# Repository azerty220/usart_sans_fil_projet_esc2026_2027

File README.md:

# Projet de Transmission UART Sans Fil

Projet Système réalisé en troisième année spécialité Electronique et Systèmes de Communication à l'ENSEA : 

> Mise en place d'une communication sans fil USART avec un drône

## Cahier des charges

L'objectif de ce projet est de concevoir une chaîne de transmission/réception RF à partir de composants existants. Cet émetteur-récepteur est destiné à la communication avec un drone. Il y a donc une contrainte de place sur au moins une des versions du système.

Contraintes générales :

    Portée du système : 10m
    Durée du projet : 40h
    Budget : 250€

Paramètres de l'USART fourni : 

    Débit : 115 200 baud
    8 bits de données
    1 bit de parité (pair)
    1 bit de stop

## Choix de la fréquence porteuse et de la modulation

Nous avons choisi une porteuse à **868MHz**, ainsi que la modulation **ASK**,    

- Notre choix s'est porté sur la modulation ASK afin d'obtenir une portée nettement supérieure. De plus, nous avons pris en compte l'expérience d'un groupe ayant réalisé ce même projet en 2025 avec la modulation BPSK : leur choix avait entraîné de lourdes difficultés, notamment au niveau de la démodulation et de la récupération de la porteuse en phase. Cette dernière nécessitait en effet une PLL sans erreur de phase, alors qu'une PLL est initialement conçue pour minimiser les erreurs de fréquence.    
- En ce qui concerne la fréquence, nous avons choisi de réutiliser les composants des années précédentes afin de réduire les coûts. De plus, opter pour la bande des 2,4 GHz très proche de la bande Wi-Fi nous aurait exposé à de nombreux signaux parasites, qui auraient été difficiles à filtrer.

# Vue d'ensemble du système émission/réception

Voici une description de notre système. Celui-ci s'organise autour d'une chaîne d'émission (composée du modulateur ASK, du PA et du filtrage) et d'une chaîne de réception (composée du filtrage, du LNA et du démodulateur ASK). Pour permettre l'utilisation d'une seule antenne dans les deux modes, les deux chaînes sont reliées par un Switch RF qui permet de passer d'un mode à l'autre. L'ensemble est piloté par un microcontrôleur µC et la porteuse elle est générée par l'oscillateur local :    

Dans un premier temps, nous avons découpé le système par fonctions : chaque binôme s'est vu assigner une tâche spécifique et devait réaliser un premier PCB (2 couches) dédié. Dans un second temps, une fois les tests validés, un PCB unique à 4 couches a été conçu pour regrouper l'ensemble du système.

# Description de la chaîne d'émission

Le rôle principal de la chaîne d'émission, consiste à traiter les données numériques reçues par liaison UART, à générer une porteuse radiofréquence à 868 MHz (stabilisée par un oscillateur local à boucle à verrouillage de phase (PLL)), puis à appliquer une modulation d'amplitude de type ASK (Amplitude Shift Keying). Le signal ainsi modulé traverse ensuite un étage de filtrage avant d'être acheminé vers l'antenne.
    <br>Le développement de cette chaîne d'émission a été structuré autour de plusieurs objectifs clés :
        <br> 1- Garantir l'intégrité et la fiabilité de la transmission des données numériques via l'interface UART.
        <br> 2- Produire un signal porteur RF stable, propre et paramétrable.
        <br> 3- Exécuter une modulation ASK fidèle aux trames de données à transmettre.
        <br> 4- Filtrer efficacement le signal radiofréquence pour respecter les normes en vigueur avant son émission par l'antenne.

## Bloc génération de la porteuse et modulation ASK

Cette partie décrit le fonctionnement des premiers bloc (Modulateur ASK et Oscillateur Local) de la chaîne détaillée précédemment, la génération de la porteuse sera réalisée par le synthétiseur de fréquence à boucle à verrouillage de phase (PLL) l’ADF4350, afin d’avoir une référence de fréquence, ce dernier sera relié à l’oscillateur ECS-TXD-20CSMV-AC-260-AY-TR et enfin pour réaliser la modulation ASK, nous utiliserons un switch RF, l’ADG918BCPZ.

### 1- interface Nucléo/PCB RF

La communication entre la carte microcontrôleur (Nucleo STM32) et le PCB RF est assurée par plusieurs connecteurs dédiés :

    <br>• Connecteur d'interface SPI (J2) : regroupant les signaux de configuration SCK (horloge de communication), DATA (données de configuration), LE (validation du registre sélectionné) et CE (activation du composant), ainsi que la masse GND, permettant le paramétrage du synthétiseur de fréquence.
    <br>• Connecteur de commande (J3) : acheminant le signal de commande UART_RX issu du microcontrôleur vers le modulateur ASK.
   <br> • Connecteur d'alimentation (J6) : fournissant les tensions +3.3V, +2V5 (utiles pour alimenter l’ADF4350, ADG918 et l’oscillateur) et la référence de masse GND à la carte.

<br>La configuration du synthétiseur de fréquence ADF4350 (U1) est réalisée via une interface série synchrone de type SPI. Cette interface permet notamment :
   <br> • l’écriture des registres de configuration de la PLL
   <br> • l’initialisation et la réinitialisation du composant
   <br> • la reprogrammation dynamique de la fréquence de sortie.

### 2- Génération de la porteuse

La génération de la porteuse radiofréquence est assurée par le composant ADF4350 (U1) d’Analog Devices. Ce circuit intègre un oscillateur commandé en tension (VCO) interne couvrant une large plage de fréquences, ainsi que l’ensemble des blocs nécessaires à la réalisation d’une PLL fractionnaire ou entière. 
<br>La référence de fréquence (26MHz) est fournie par l’oscillateur à quartz Y1 (ECS-TXD-20CSMV-AC-260-AY-TR) connecté à l’entrée REFIN via le condensateur C24 (capacité bouchon de 1 nF). Dans cette application, l’ADF4350 est configuré pour fournir une porteuse à 868 MHz.

### 3- Modulation ASK
<br>-> SMA vers le PCB amplificateur de puissance et filtrage
<br> Vue d'ensemble du PCB

## Bloc amplificateur de puissance et filtrage

La sortie du modulateur est réglable en puissance entre -4dBm et 5dBm, ce qui n'est pas suffisant pour atteindre la portée voulue. 

Nous avions en stock des amplificateurs SKY66185-11, utilisés pour un projet semblable l'année précédente. Ces amplificateurs Skyworks à forte linéarité fournissent un gain supplémentaire de $36.5$ dB, sur une bande de  $851$ à $894$ MHz.

> Bilan de puissance à faire

Ce signal amplifié passe ensuite dans un filtre de mise en forme, le SF2425E.

Premier PCB de test :

# Switch RF et antenne

Commutation entre les 2 modes -> Johan

# Description de la chaîne de réception

choix des composants modules par module

## Bloc filtrage et LNA

Le signal capté par l'antenne est amplifié par le LNA **GRF2070**, puis filtré par le filtre SAW **SF2425E** centré sur 868,6 MHz.

```mermaid
flowchart LR
    A((Antenne)) --> LNA[["LNA GRF2070<br/>G = 21 dB · NF = 0,4 dB"]]
    LNA --> SAW[["Filtre SAW SF2425E<br/>BP ≈ 1,5 MHz · IL ≈ 2,65 dB"]]
    SAW --> D[Démodulateur ASK]
    style LNA fill:#dbeafe,stroke:#2563eb
    style SAW fill:#dcfce7,stroke:#16a34a
```

<p align="center">

| Réf.            | Valeur                        | Rôle                                                |
|:---------------:|:-----------------------------:|:--------------------------------------------------- |
| C1 / C2         | 47 pF / 4,7 pF                | Liaison entrée / sortie du LNA (blocage du continu) |
| R2              | 910 Ω                         | Polarisation : fixe I<sub>DD</sub> ≈ 70 mA sous 5 V |
| L1              | 22 nH                         | Self de choc : amène le 5 V sur `RF_OUT/VDD`        |
| C3 / C4         | 100 nF / 100 pF               | Découplage BF / HF                                  |
| L2, C6 / L3, C7 | 22 nH, 2,7 pF / 33 nH, 3,9 pF | Adaptation 50 Ω ↔ filtre SAW (≈ 386 Ω ∥ 1,6 pF)     |

**Pourquoi LNA → filtre ?** D'après la formule de Friis, $F = F_1 + (F_2-1)/G_1$. Placé derrière 21 dB de gain, le filtre ne dégrade presque pas le bruit : **NF ≈ 0,43 dB**, contre ≈ 3 dB si le filtre était placé avant le LNA. Le signal ASK à 115,2 kbaud occupe environ 230 kHz et passe sans déformation dans la bande de 1,5 MHz du filtre.

| Chaîne complète | Gain ≈ **18,4 dB** | NF ≈ **0,43 dB** | Alim. **5 V / 70 mA** |
|:--------------- |:------------------:|:----------------:|:---------------------:|

## Bloc Démodulateur

### 1. Présentation et choix du composant

Ce PCB a été conçu sous **KiCad 9.0** pour réaliser la démodulation d'un signal radiofréquence modulé en amplitude (**ASK**), dans le cadre du projet de transmission USART sans fil entre une station au sol et un drone.

Le circuit repose sur l'**AD8313 d'Analog Devices**, un détecteur logarithmique RF fonctionnant sur une plage de fréquences de **100 MHz à 2,5 GHz**.

Ce composant a été choisi pour :

- Sa compatibilité avec les fréquences envisagées de **868 MHz et 918 MHz**.
- Sa capacité à détecter des signaux RF de faible puissance.
- Sa sortie analogique permettant de récupérer l'enveloppe du signal ASK.
- Son faible encombrement, adapté à la conception d'un PCB compact.

Le PCB intègre également un réseau d'adaptation RF, des condensateurs de découplage et un plan de masse sur la couche **B.Cu**.

### 2. Connecteur SMA – Entrée RF (J2)

Le connecteur **SMA J2** constitue l'entrée radiofréquence du PCB.

Il permet de raccorder une antenne ou un générateur RF à l'aide d'un câble coaxial de **50 Ω**.

Le signal reçu traverse le condensateur de liaison **C2 (680 pF)**, qui bloque la composante continue, avant d'atteindre l'entrée **INHI** de l'AD8313.

La résistance **R2 (53,6 Ω)** participe à l'adaptation de l'entrée RF à une impédance proche de 50 Ω afin de limiter les réflexions.

Le connecteur SMA a été choisi pour faciliter les tests avec les équipements RF disponibles au laboratoire.

### 3. Connecteur J3 – Alimentation et sortie démodulée

Le connecteur **J3 à trois broches** regroupe l'alimentation, la masse et la sortie du démodulateur.

| Broche | Signal    | Fonction                    |
| ------ | --------- | --------------------------- |
| 1      | VCC_demod | Alimentation du circuit     |
| 2      | GND       | Masse commune               |
| 3      | demodOUT  | Sortie analogique démodulée |

L'alimentation des deux broches **VPOS** de l'AD8313 passe par les résistances **R1 et R3 (10 Ω)**, associées aux condensateurs de découplage **C1 et C4 (100 nF)** pour réduire les perturbations sur l'alimentation.

La sortie **VOUT** est reliée à **VSET** par une résistance de **0 Ω (R4)** et traverse une résistance de protection **Rprot1 (500 Ω)** avant d'atteindre le connecteur J3.

Une résistance **RL1 (1 MΩ)** est également connectée entre la sortie et la masse.

Ce connecteur facilite l'intégration du démodulateur avec les autres blocs du système de communication.
Voici sa visualisation en 3D

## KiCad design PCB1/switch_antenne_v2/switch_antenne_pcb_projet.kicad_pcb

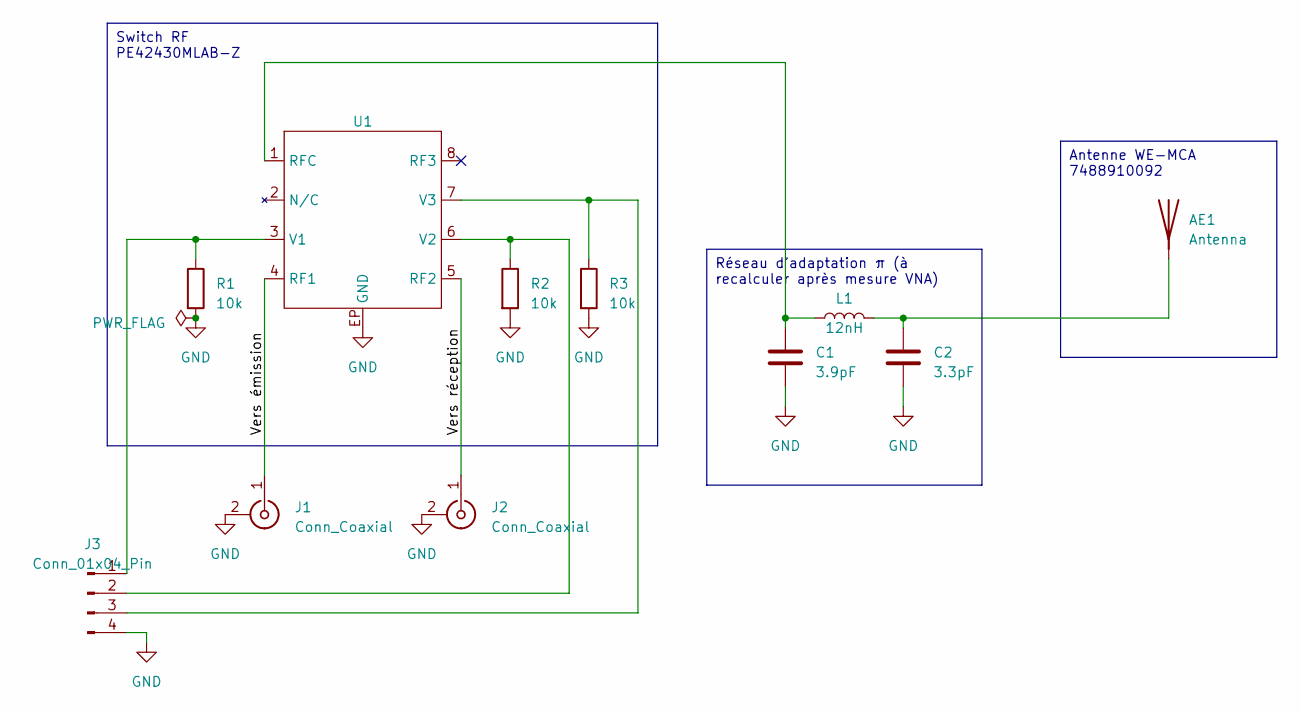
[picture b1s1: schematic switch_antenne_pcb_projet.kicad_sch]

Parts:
AE1: Antenna; AE_Wurth_WE-MCA_7488910092
C1: 3.9pF; C_0402_1005Metric_Pad0.74x0.62mm_HandSolder
C2: 3.3pF; C_0402_1005Metric_Pad0.74x0.62mm_HandSolder
J1, J2: Conn_Coaxial; SMA_Samtec_SMA-J-P-X-ST-EM1_EdgeMount
J3: Conn_01x04_Pin; PinHeader_1x04_P2.54mm_Vertical
L1: 12nH; L_0402_1005Metric_Pad0.77x0.64mm_HandSolder
R1, R2, R3: 10k; R_0603_1608Metric_Pad0.98x0.95mm_HandSolder
U1: SON50P200X200X60-9N160X90

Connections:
/Vers réception: J2.1 (In), U1.5 (RF2)
/Vers émission: J1.1 (In), U1.4 (RF1)
GND: C1.2, C2.2, J1.2 (Ext), J2.2 (Ext), J3.4, R1.2, R2.2, R3.2, U1.EP (GND)
unnamed: AE1.2 (A), C2.1, L1.2
unnamed: J3.1, R1.1, U1.3 (V1)
unnamed: J3.2, R2.1, U1.6 (V2)
unnamed: J3.3, R3.1, U1.7 (V3)
unnamed: C1.1, L1.1, U1.1 (RFC)

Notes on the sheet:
Switch RF PE42430MLAB-Z
Réseau d’adaptation π (à recalculer après mesure VNA)
Antenne WE-MCA 7488910092

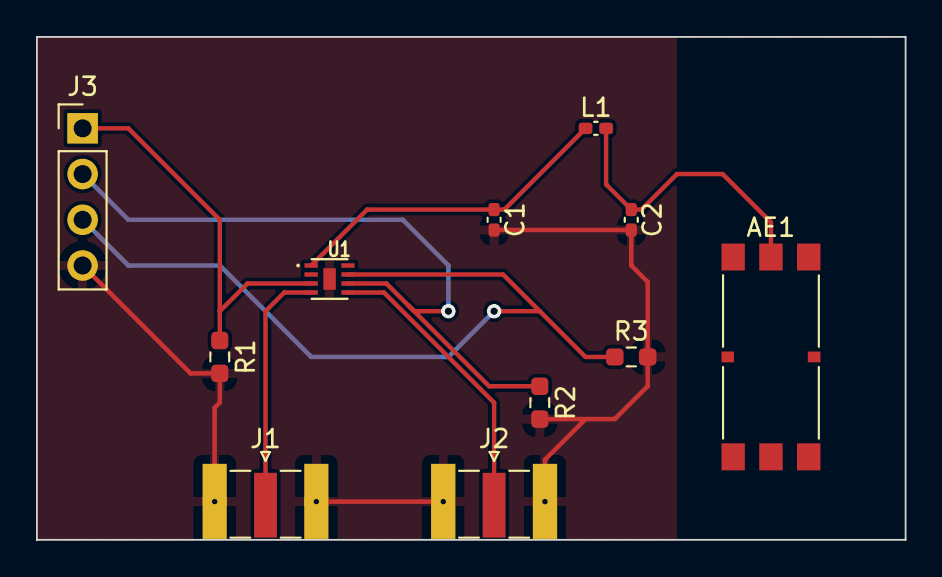
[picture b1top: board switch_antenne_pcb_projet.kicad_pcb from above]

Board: 2 copper layers, 48.3 x 27.9 mm, 11 parts (0 on the bottom side), 8 nets.

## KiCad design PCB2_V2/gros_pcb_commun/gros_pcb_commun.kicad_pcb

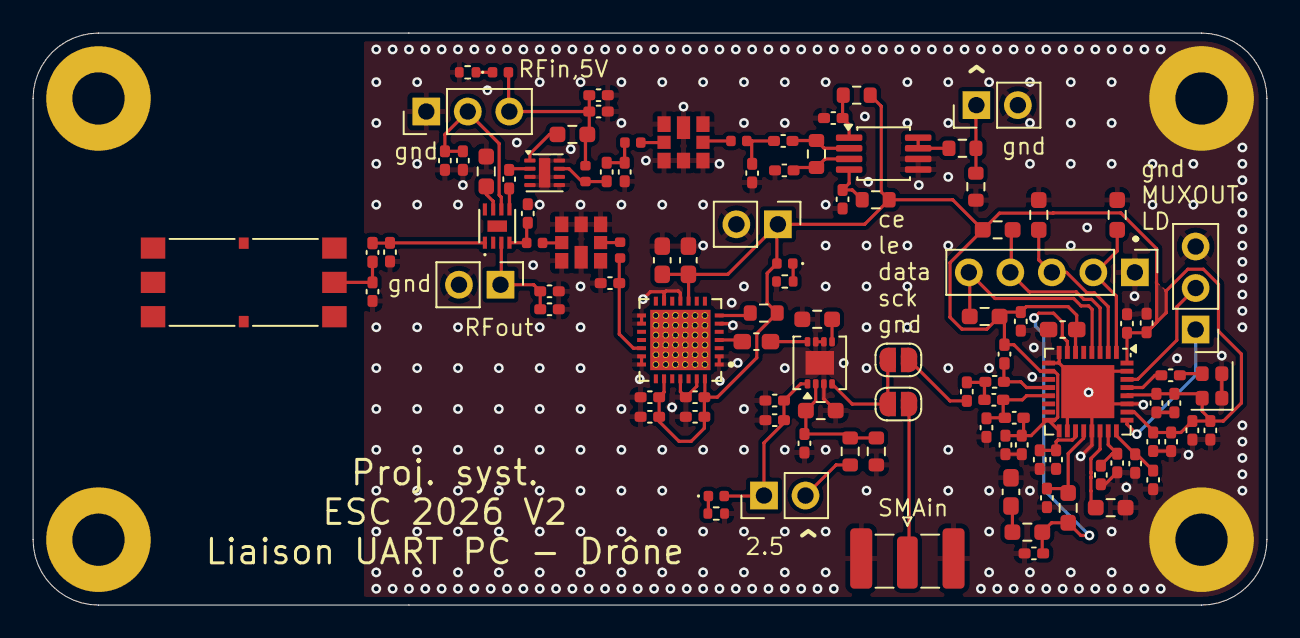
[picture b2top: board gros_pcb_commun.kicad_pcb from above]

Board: 2 copper layers, 75.5 x 35.0 mm, 111 parts (0 on the bottom side), 57 nets.

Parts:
AE1: Antenna; AE_Wurth_WE-MCA_7488910092
C1, C3, C5, C7, C9: 100 nF; C_0402_1005Metric_Pad0.74x0.62mm_HandSolder
C2, C4, C6, C10, C13, C15, C17, C27: 10 pF; C_0402_1005Metric_Pad0.74x0.62mm_HandSolder
C8: 10 pF; C_0603_1608Metric_Pad1.08x0.95mm_HandSolder
C11: 1 uF; C_0402_1005Metric_Pad0.74x0.62mm_HandSolder
C12, C14, C16, C18, C28, C42, C43: 0.1 uF; C_0402_1005Metric_Pad0.74x0.62mm_HandSolder
C19: 1 nF; C_0402_1005Metric_Pad0.74x0.62mm_HandSolder
C20, C21: 4 pF; C_0402_1005Metric_Pad0.74x0.62mm_HandSolder
C22: 120 pF; C_0402_1005Metric_Pad0.74x0.62mm_HandSolder
C23: 42.3 nF; C_0402_1005Metric_Pad0.74x0.62mm_HandSolder
C24: 575 nF; C_0603_1608Metric_Pad1.08x0.95mm_HandSolder
C25: 19.3 nF; C_0402_1005Metric_Pad0.74x0.62mm_HandSolder
C26: 100 pF; C_0402_1005Metric_Pad0.74x0.62mm_HandSolder
C29, C32, C35, C36, C50, C53: 0.1u; C_0402_1005Metric_Pad0.74x0.62mm_HandSolder
C30: 2.7p; C_0402_1005Metric_Pad0.74x0.62mm_HandSolder
C31: 33p; C_0603_1608Metric_Pad1.08x0.95mm_HandSolder
C33, C37: 10u; C_0603_1608Metric_Pad1.08x0.95mm_HandSolder
C34: 3.5p; C_0402_1005Metric_Pad0.74x0.62mm_HandSolder
C38: 3.9pF; C_0402_1005Metric_Pad0.74x0.62mm_HandSolder
C39: 3.3pF; C_0402_1005Metric_Pad0.74x0.62mm_HandSolder
C40, C41: 680 pF; C_0402_1005Metric_Pad0.74x0.62mm_HandSolder
C44: 47pF; C_0402_1005Metric_Pad0.74x0.62mm_HandSolder
C45: 4.7pF; C_0402_1005Metric_Pad0.74x0.62mm_HandSolder
C46: 100nF; C_0402_1005Metric_Pad0.74x0.62mm_HandSolder
C47: 100pF; C_0402_1005Metric_Pad0.74x0.62mm_HandSolder
C48: 2,7pF; C_0402_1005Metric_Pad0.74x0.62mm_HandSolder
C49: 3,5pF; C_0402_1005Metric_Pad0.74x0.62mm_HandSolder
C51, C52: 10u; C_0402_1005Metric_Pad0.74x0.62mm_HandSolder
D1, D2, D3: LED_Small; LED_0402_1005Metric
FL1: SF2425E
H1, H2, H3, H4: MountingHole_Pad; MountingHole_3.2mm_M3_Pad
J1, J2, J6, J7: Conn_01x02_Pin; PinHeader_1x02_P2.54mm_Vertical
J3: Conn_01x05; PinHeader_1x05_P2.54mm_Vertical
J4: Conn_01x03; PinHeader_1x03_P2.54mm_Vertical
J5: Conn_Coaxial; SMA_Samtec_SMA-J-P-H-ST-EM1_EdgeMount
J9: Conn_01x03_Pin; PinHeader_1x03_P2.54mm_Vertical
JP1, JP2: SolderJumper_2_Open; SolderJumper-2_P1.3mm_Open_RoundedPad1.0x1.5mm
L1: 68 nH; L_0402_1005Metric_Pad0.77x0.64mm_HandSolder
L2, L3: 18 nH; L_0402_1005Metric_Pad0.77x0.64mm_HandSolder
L4, L5: 24n; L_0402_1005Metric
L6: 12nH; L_0402_1005Metric_Pad0.77x0.64mm_HandSolder
L7, L8, L9: 22nH; L_0402_1005Metric
R1, R2, R3, R5, R8, R13: 10k; R_0603_1608Metric_Pad0.98x0.95mm_HandSolder
R4: 5.1 k; R_0603_1608Metric_Pad0.98x0.95mm_HandSolder
R6: 59.7; R_0603_1608Metric_Pad0.98x0.95mm_HandSolder
R7: 122; R_0603_1608Metric_Pad0.98x0.95mm_HandSolder
R9: 50; R_0603_1608Metric_Pad0.98x0.95mm_HandSolder
R10: 5k1; R_0603_1608Metric
R11: 32; R_0603_1608Metric
R12: 100; R_0603_1608Metric
R14, R17: 10; R_0603_1608Metric
R15: 53,6; R_0603_1608Metric
R16, R19, R20: R_Small; R_0402_1005Metric
R18: 910; R_0603_1608Metric_Pad0.98x0.95mm_HandSolder
RL1: 1M; R_0603_1608Metric
Rprot1: 500; R_0603_1608Metric
SF1: SF2425E
U1: ADF4350; LFCSP-32-1EP_5x5mm_P0.5mm_EP3.25x3.25mm
U2: ADG918BCPZ; LFCSP-8-1EP_3x3mm_P0.5mm_EP1.45x1.74mm
U3: SKY66185-11; IC_SKY66185-11
U4: SON50P200X200X60-9N160X90
U5: AD8313xRM; MSOP-8_3x3mm_P0.65mm
U6: GRF2070; DFN-8-2x2mm_P0.7mm
Y1: ECS-TXO-20CSMV-AC-260-AY-TR; Oscillator_SMD_SiT_PQFN-4Pin_2.0x1.6mm

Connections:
+2V5: C27.1, C28.1, D3.2 (A), J1.1, U2.1 (VDD)
+5V: C46.1, C47.1, D1.2 (A), J9.3, L7.1, R18.1
A+: C20.1, L2.2, U1.12 (RF_OUT_A+)
A-: C21.1, L1.2, L3.2, U1.13 (RF_OUT_A-)
AVDD: C1.2, C2.2, C3.2, C4.2, C5.2, C6.2, C7.2, C8.2, C9.2, C10.2, C11.1, C12.1, C29.2, C32.2, C33.2, C35.1, C36.1, C37.1, D2.2 (A), J6.1, L1.1, L2.1, R1.2, R2.1, R10.1, R14.1, R17.2, U1.6 (Vp), U1.10 (AVDD), U1.16 (VVCO), U1.17 (VVCO), U1.26 (PDB_RF), U1.28 (DVDD), U1.32 (SDVDD), U3.10 (VBIAS), U3.23 (VCC3), U3.28 (VCC1), Y1.4 (VDD)
CE: J3.5, R2.2, U1.4 (CE)
DATA: J3.3, R3.1, U1.2 (DATA)
FiltreIN: C30.1, L4.1, U3.19 (RFOUT)
GND: C1.1, C2.1, C3.1, C4.1, C5.1, C6.1, C7.1, C8.1, C9.1, C10.1, C11.2, C12.2, C13.2, C14.2, C15.2, C16.2, C17.2, C18.2, C21.2, C23.2, C24.2, C25.2, C26.2, C27.2, C28.2, C29.1, C30.2, C32.1, C33.1, C34.2, C35.2, C36.2, C37.2, C38.2, C39.2, C41.1, C42.2, C43.1, C46.2, C47.2, C48.2, C49.1, C50.1, C51.1, C52.1, C53.1, FL1.1 (IN_GND), FL1.3 (GND), FL1.4 (GND), FL1.5 (OUT_GND), FL1.7 (GND), FL1.8 (GND), H1.1, H3.1, J2.2, J3.1, J4.3, J5.2 (Ext), J6.2, J7.2, J9.1, R3.2, R4.1, R5.2, R8.2, R9.2, R12.1, R13.2, R16.2, R19.2, R20.2, RL1.1, SF1.1 (IN_GND), SF1.3 (GND), SF1.4 (GND), SF1.5 (OUT_GND), SF1.7 (GND), SF1.8 (GND), U1.8 (CPGND), U1.9 (AGND), U1.11 (AGNDVCO), U1.18 (AGNDVCO), U1.21 (AGNDVCO), U1.27 (DGND), U1.31 (SDGND), U1.33 (EP), U2.3 (GND), U2.6 (GND), U2.7 (GND), U2.9 (GND), U3.1 (GND), U3.2 (GND), U3.6 (GND), U3.11 (GND), U3.13 (GND), U3.15 (GND), U3.16 (GND), U3.20 (GND), U3.21 (GND), U3.25 (GND), U3.27 (GND), U5.5 (PWDN), U5.6 (COMM), U6.3 (GND), U6.4 (GND), U6.5 (GND), U6.6 (GND), U6.8 (GND), U6.9 (EP), Y1.1 (GROUND_1), Y1.2 (GROUND_2)
LE: J3.4, R1.1, U1.3 (LE)
unnamed: AE1.2 (A), C39.1, L6.2
unnamed: C20.2, C22.1, L3.1
unnamed: C24.1, R6.2
unnamed: C42.1, R14.2, U5.1 (VPOS)
unnamed: C43.2, R17.1, U5.4 (VPOS)
unnamed: C45.2, C48.1, L8.1
unnamed: D1.1 (K), R16.1
unnamed: D2.1 (K), R19.1
unnamed: D3.1 (K), R20.1
unnamed: FL1.2 (IN), L8.2
unnamed: FL1.6 (OUT), L9.1
unnamed: J4.1, U1.25 (LD)
unnamed: J4.2, U1.30 (MUXOUT)
unnamed: J5.1 (In), JP1.1 (A)
unnamed: L4.2, SF1.2 (IN)
unnamed: L5.1, SF1.6 (OUT)
unnamed: C23.1, R6.1, R7.2, U1.7 (CPout)
unnamed: R4.2, U1.22 (RSET)
unnamed: C25.1, R7.1, U1.20 (VTUNE)
unnamed: R9.1, U2.5 (RF2)
unnamed: C31.2, U3.4 (RFIN)
unnamed: R10.2, U3.7 (~VEN)
unnamed: C38.1, L6.1, U4.1 (RFC)
unnamed: R13.1, U4.7 (V3)
unnamed: C40.2, R15.1, U5.2 (INHI)
unnamed: C41.2, R15.2, U5.3 (INLO)
unnamed: Rprot1.1, U5.7 (VSET), U5.8 (VOUT)
unnamed: C44.2, U6.2 (RF_IN)
unnamed: C45.1, L7.2, U6.7 (RF_OUT/VDD)
unnamed: R18.2, U6.1 (VENABLE)
unnamed: C19.1, Y1.3 (OUTPUT)
Porteuse_RFC: C22.2, JP2.1 (A)
Porteuse_RFC_ap: JP1.2 (B), JP2.2 (B), U2.4 (RFC)
REFIN: C19.2, U1.29 (REFIN)
SCK: J3.2, R5.1, U1.1 (CLK)
TEMP: C13.1, C14.1, U1.19 (TEMP)
V1: C52.2, C53.2, J2.1, U4.3 (V1)
V2: C50.2, C51.2, J9.2, U4.6 (V2)
VCOM: C15.1, C16.1, U1.23 (VCOM)
VREF: C17.1, C18.1, U1.24 (VREF)
sig0: C26.1, R8.1, R11.2, R12.2, U2.2 (CTRL)
sig0_pont: J1.2, R11.1
sig1: C31.1, U2.8 (RF1)
sig2: C34.1, L5.2, U4.4 (RF1)
sig3: C44.1, U4.5 (RF2)
sig4: C40.1, C49.2, L9.2
sig5: J7.1, RL1.2, Rprot1.2

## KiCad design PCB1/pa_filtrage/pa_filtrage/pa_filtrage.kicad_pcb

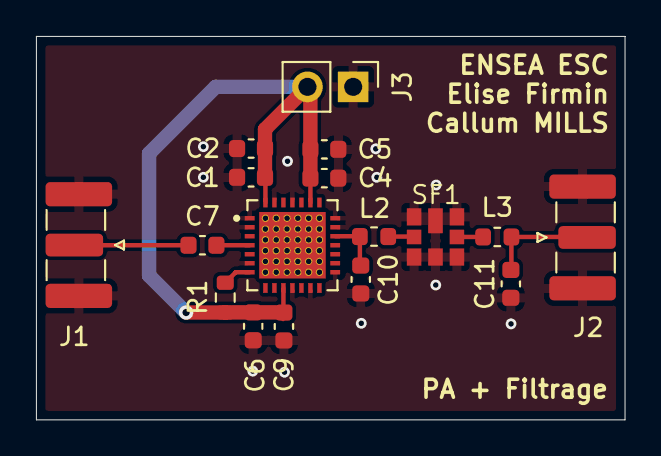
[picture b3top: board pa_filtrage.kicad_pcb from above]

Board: 2 copper layers, 32.7 x 21.3 mm, 17 parts (0 on the bottom side), 9 nets.

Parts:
C1, C4, C6: 0.1u; C_0603_1608Metric
C2, C5: 10u; C_0603_1608Metric
C7: 33p; C_0603_1608Metric
C9: 0.1u x2; C_0603_1608Metric
C10: 2.7p; C_0603_1608Metric
C11: 3.5p; C_0603_1608Metric
J1, J2: Conn_Coaxial; SMA_Samtec_SMA-J-P-H-ST-EM1_EdgeMount
J3: Conn_01x02_Pin; PinHeader_1x02_P2.54mm_Vertical
L2, L3: 24n; L_0603_1608Metric
R1: 5k1; R_0603_1608Metric
SF1: SF2425E
U1: SKY66185-11; IC_SKY66185-11

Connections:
+3.3V: C1.2, C2.2, C4.1, C5.1, C6.2, C9.1, J3.2, R1.1, U1.10 (VBIAS), U1.23 (VCC3), U1.28 (VCC1)
FiltreIN: C10.1, L2.1, U1.19 (RFOUT)
FiltreOUT: C11.1, J2.1 (In), L3.2
GND: C1.1, C2.1, C4.2, C5.2, C6.1, C9.2, C10.2, C11.2, J1.2 (Ext), J2.2 (Ext), J3.1, SF1.1 (IN_GND), SF1.3 (GND), SF1.4 (GND), SF1.5 (OUT_GND), SF1.7 (GND), SF1.8 (GND), U1.1 (GND), U1.2 (GND), U1.6 (GND), U1.11 (GND), U1.13 (GND), U1.15 (GND), U1.16 (GND), U1.20 (GND), U1.21 (GND), U1.25 (GND), U1.27 (GND)
unnamed: L2.2, SF1.2 (IN)
unnamed: L3.1, SF1.6 (OUT)
unnamed: C7.2, U1.4 (RFIN)
unnamed: R1.2, U1.7 (~VEN)
RFIN: C7.1, J1.1 (In)

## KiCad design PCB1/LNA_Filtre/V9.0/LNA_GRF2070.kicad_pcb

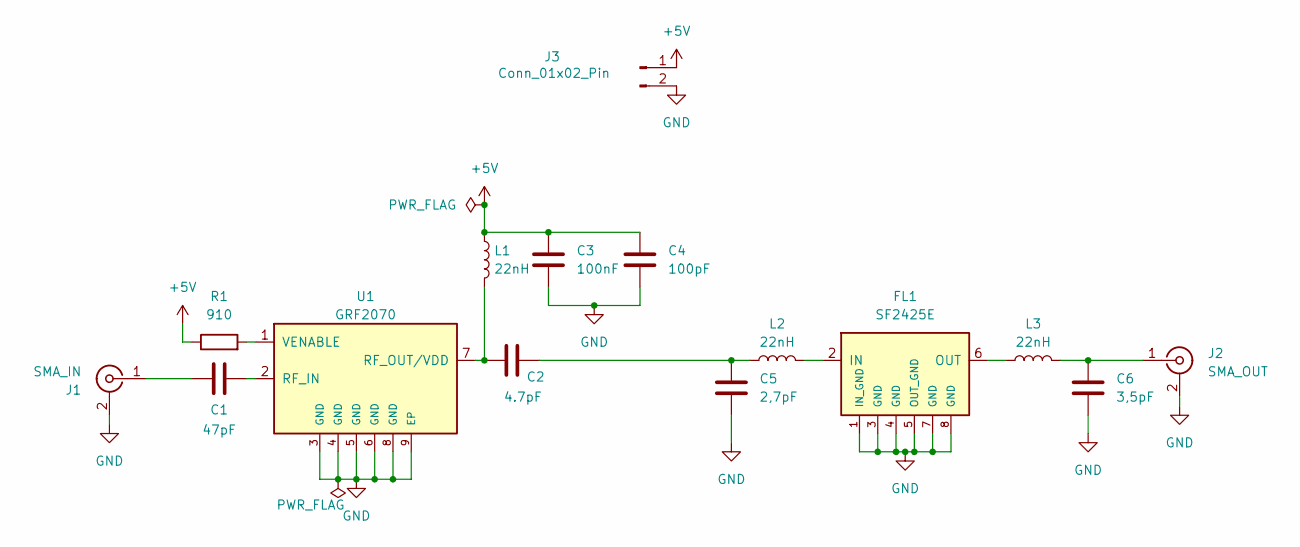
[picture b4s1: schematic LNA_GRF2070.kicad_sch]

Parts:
C1: 47pF; C_0603_1608Metric
C2: 4.7pF; C_0603_1608Metric
C3: 100nF; C_0603_1608Metric
C4: 100pF; C_0603_1608Metric
C5: 2,7pF; C_0603_1608Metric
C6: 3,5pF; C_0603_1608Metric
FL1: SF2425E
J1: SMA_IN; SMA_Samtec_SMA-J-P-H-ST-EM1_EdgeMount
J2: SMA_OUT; SMA_Samtec_SMA-J-P-H-ST-EM1_EdgeMount
J3: Conn_01x02_Pin; PinHeader_1x02_P2.54mm_Vertical
L1, L2, L3: 22nH; L_0603_1608Metric
R1: 910; R_0603_1608Metric_Pad0.98x0.95mm_HandSolder
U1: GRF2070; WDFN-8-1EP_2x2.2mm_P0.5mm_EP0.80x0.54

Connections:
+5V: C3.1, C4.1, J3.1, L1.1, R1.1
GND: C3.2, C4.2, C5.2, C6.1, FL1.1 (IN_GND), FL1.3 (GND), FL1.4 (GND), FL1.5 (OUT_GND), FL1.7 (GND), FL1.8 (GND), J1.2 (Ext), J2.2 (Ext), J3.2, U1.3 (GND), U1.4 (GND), U1.5 (GND), U1.6 (GND), U1.8 (GND), U1.9 (EP)
unnamed: C2.2, C5.1, L2.1
unnamed: FL1.2 (IN), L2.2
unnamed: FL1.6 (OUT), L3.1
unnamed: C1.1, J1.1 (In)
unnamed: C6.2, J2.1 (In), L3.2
unnamed: C1.2, U1.2 (RF_IN)
unnamed: C2.1, L1.2, U1.7 (RF_OUT/VDD)
unnamed: R1.2, U1.1 (VENABLE)

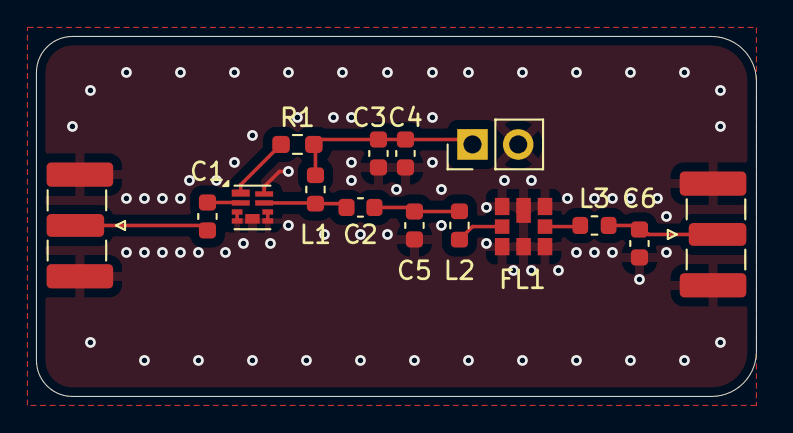
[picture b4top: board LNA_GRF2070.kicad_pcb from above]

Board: 2 copper layers, 40.0 x 20.0 mm, 15 parts (0 on the bottom side), 10 nets.

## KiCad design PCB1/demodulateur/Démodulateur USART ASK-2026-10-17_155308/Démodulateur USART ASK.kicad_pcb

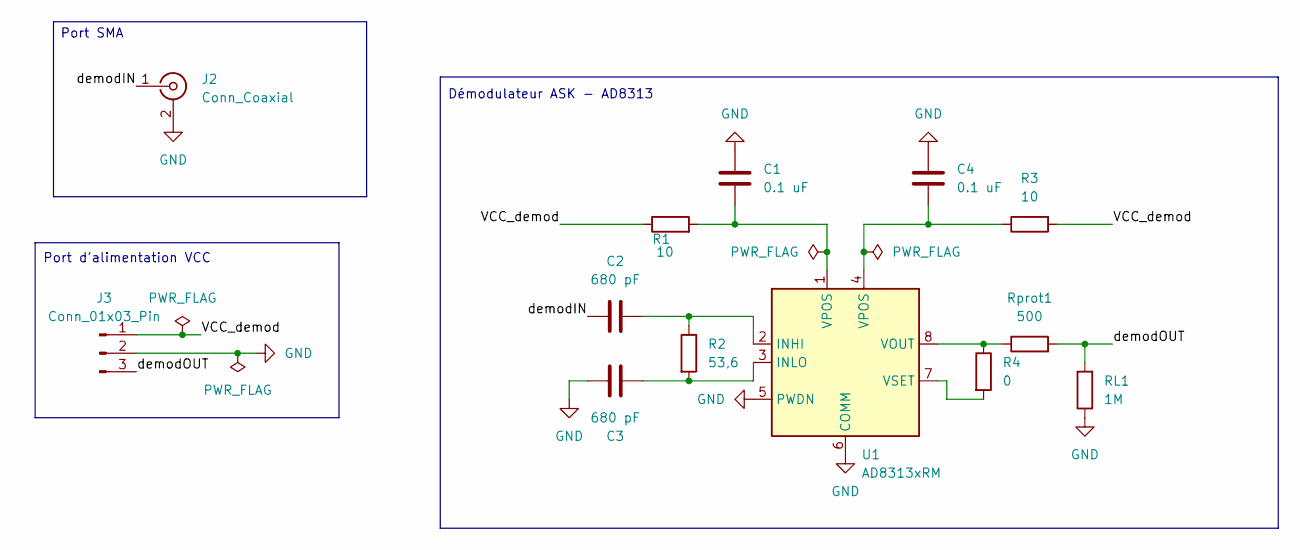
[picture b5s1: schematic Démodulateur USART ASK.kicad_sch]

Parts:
C1, C4: 0.1 uF; C_0603_1608Metric
C2, C3: 680 pF; C_0603_1608Metric
J2: Conn_Coaxial; SMA_Samtec_SMA-J-P-H-ST-EM1_EdgeMount
J3: Conn_01x03_Pin; PinHeader_1x03_P2.54mm_Vertical
R1, R3: 10; R_0603_1608Metric
R2: 53,6; R_0603_1608Metric
R4: 0; R_0603_1608Metric
RL1: 1M; R_0603_1608Metric
Rprot1: 500; R_0603_1608Metric
U1: AD8313xRM; MSOP-8_3x3mm_P0.65mm

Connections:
/VCC_demod: J3.1, R1.1, R3.2
/demodIN: C2.1, J2.1 (In)
/demodOUT: J3.3, RL1.2, Rprot1.2
GND: C1.2, C3.1, C4.1, J2.2 (Ext), J3.2, RL1.1, U1.5 (PWDN), U1.6 (COMM)
unnamed: C1.1, R1.2, U1.1 (VPOS)
unnamed: C4.2, R3.1, U1.4 (VPOS)
unnamed: C2.2, R2.1, U1.2 (INHI)
unnamed: C3.2, R2.2, U1.3 (INLO)
unnamed: R4.1, Rprot1.1, U1.8 (VOUT)
unnamed: R4.2, U1.7 (VSET)

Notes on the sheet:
Démodulateur ASK - AD8313
Port d'alimentation VCC
Port SMA

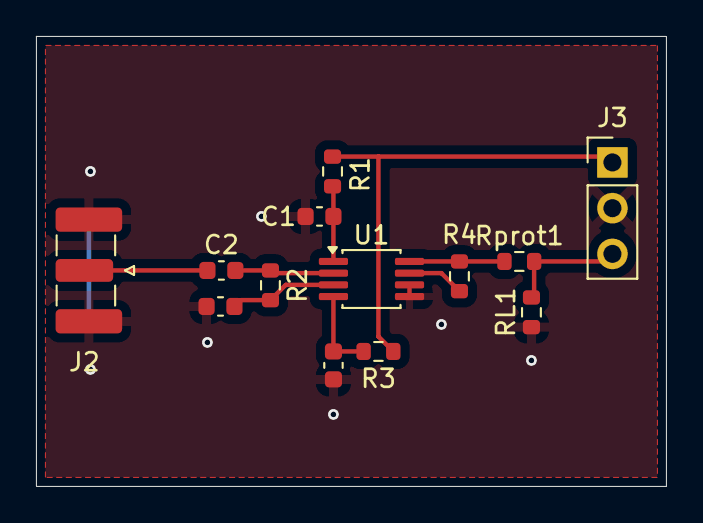
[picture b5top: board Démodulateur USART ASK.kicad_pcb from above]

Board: 2 copper layers, 35.0 x 25.0 mm, 13 parts (0 on the bottom side), 10 nets.

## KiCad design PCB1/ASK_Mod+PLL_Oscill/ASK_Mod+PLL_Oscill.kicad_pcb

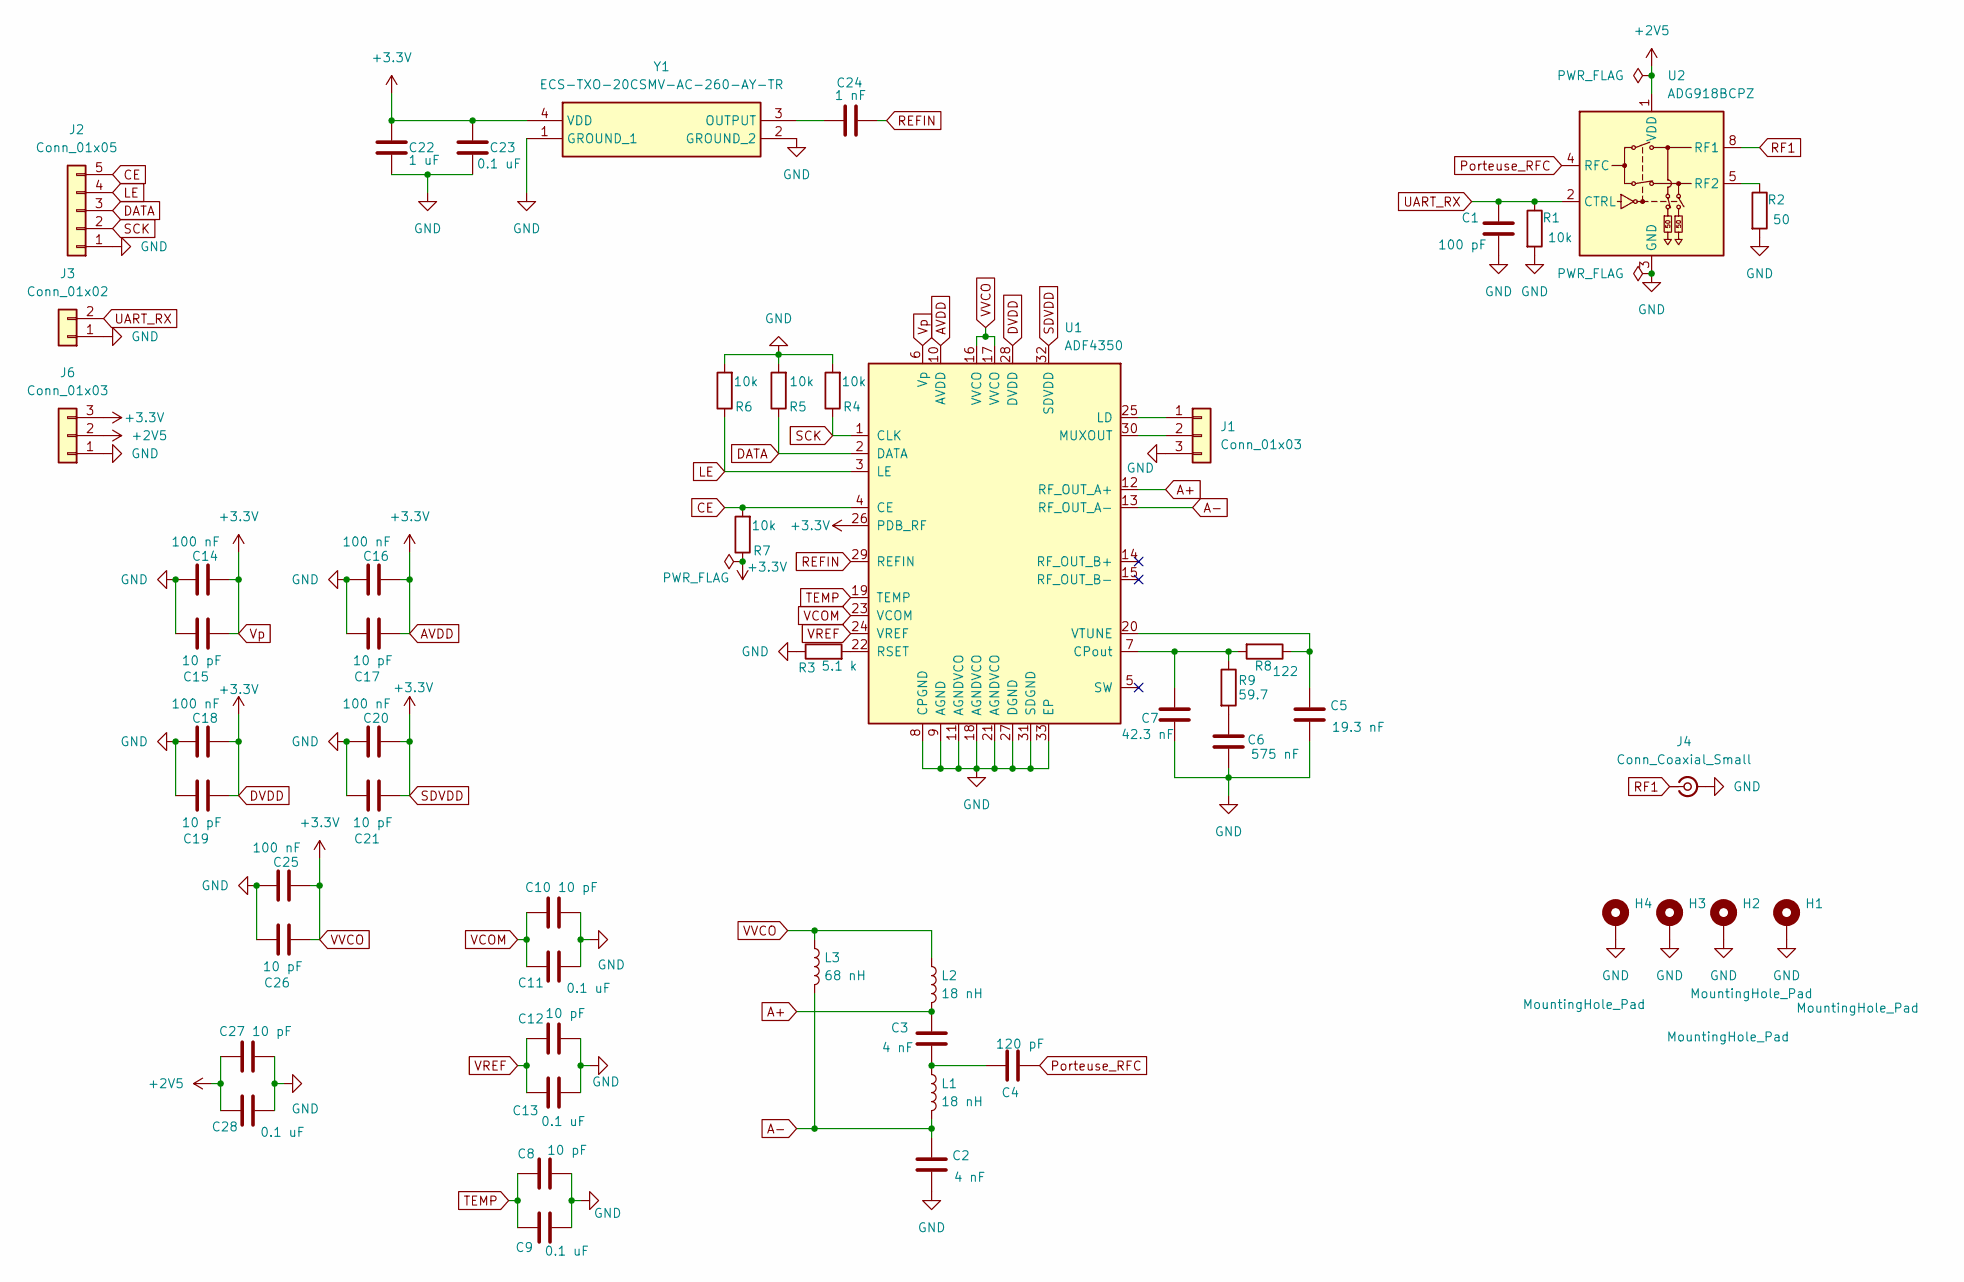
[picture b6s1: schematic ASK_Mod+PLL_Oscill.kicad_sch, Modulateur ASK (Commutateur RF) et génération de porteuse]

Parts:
C1: 100 pF; C_0603_1608Metric_Pad1.08x0.95mm_HandSolder
C2, C3: 4 nF; C_0603_1608Metric_Pad1.08x0.95mm_HandSolder
C4: 120 pF; C_0603_1608Metric_Pad1.08x0.95mm_HandSolder
C5: 19.3 nF; C_0603_1608Metric_Pad1.08x0.95mm_HandSolder
C6: 575 nF; C_0603_1608Metric_Pad1.08x0.95mm_HandSolder
C7: 42.3 nF; C_0603_1608Metric_Pad1.08x0.95mm_HandSolder
C8, C10, C12, C15, C17, C19, C21, C26, C27: 10 pF; C_0603_1608Metric_Pad1.08x0.95mm_HandSolder
C9, C11, C13, C23, C28: 0.1 uF; C_0603_1608Metric_Pad1.08x0.95mm_HandSolder
C14, C16, C18, C20, C25: 100 nF; C_0603_1608Metric_Pad1.08x0.95mm_HandSolder
C22: 1 uF; C_0603_1608Metric_Pad1.08x0.95mm_HandSolder
C24: 1 nF; C_0603_1608Metric_Pad1.08x0.95mm_HandSolder
H1, H2, H3, H4: MountingHole_Pad; MountingHole_3.2mm_M3_Pad
J1, J6: Conn_01x03; PinHeader_1x03_P2.54mm_Vertical
J2: Conn_01x05; PinHeader_1x05_P2.54mm_Vertical
J3: Conn_01x02; PinHeader_1x02_P2.54mm_Vertical
J4: Conn_Coaxial_Small; SMA_Samtec_SMA-J-P-H-ST-EM1_EdgeMount
L1, L2: 18 nH; L_0402_1005Metric_Pad0.77x0.64mm_HandSolder
L3: 68 nH; L_0402_1005Metric_Pad0.77x0.64mm_HandSolder
R1, R4, R5, R6, R7: 10k; R_0603_1608Metric_Pad0.98x0.95mm_HandSolder
R2: 50; R_0603_1608Metric_Pad0.98x0.95mm_HandSolder
R3: 5.1 k; R_0603_1608Metric_Pad0.98x0.95mm_HandSolder
R8: 122; R_0603_1608Metric_Pad0.98x0.95mm_HandSolder
R9: 59.7; R_0603_1608Metric_Pad0.98x0.95mm_HandSolder
U1: ADF4350; LFCSP-32-1EP_5x5mm_P0.5mm_EP3.25x3.25mm
U2: ADG918BCPZ; LFCSP-8-1EP_3x3mm_P0.5mm_EP1.45x1.74mm
Y1: ECS-TXO-20CSMV-AC-260-AY-TR; Oscillator_SMD_SiT_PQFN-4Pin_2.0x1.6mm; Mouser Part Number 520-T20CSMVAC260AYTR

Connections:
+2V5: C27.1, C28.1, J6.2, U2.1 (VDD)
A+: C3.1, L2.2, U1.12 (RF_OUT_A+)
A-: C2.1, L1.2, L3.2, U1.13 (RF_OUT_A-)
AVDD: C14.2, C15.2, C16.2, C17.2, C18.2, C19.2, C20.2, C21.2, C22.1, C23.1, C25.2, C26.2, J6.3, L2.1, L3.1, R7.1, U1.6 (Vp), U1.10 (AVDD), U1.16 (VVCO), U1.17 (VVCO), U1.26 (PDB_RF), U1.28 (DVDD), U1.32 (SDVDD), Y1.4 (VDD)
CE: J2.5, R7.2, U1.4 (CE)
DATA: J2.3, R5.1, U1.2 (DATA)
GND: C1.2, C2.2, C5.2, C6.2, C7.2, C8.2, C9.2, C10.2, C11.2, C12.2, C13.2, C14.1, C15.1, C16.1, C17.1, C18.1, C19.1, C20.1, C21.1, C22.2, C23.2, C25.1, C26.1, C27.2, C28.2, H1.1, H2.1, H3.1, H4.1, J1.3, J2.1, J3.1, J4.2 (Ext), J6.1, R1.2, R2.2, R3.1, R4.2, R5.2, R6.2, U1.8 (CPGND), U1.9 (AGND), U1.11 (AGNDVCO), U1.18 (AGNDVCO), U1.21 (AGNDVCO), U1.27 (DGND), U1.31 (SDGND), U1.33 (EP), U2.3 (GND), U2.6 (GND), U2.7 (GND), U2.9 (GND), Y1.1 (GROUND_1), Y1.2 (GROUND_2)
LE: J2.4, R6.1, U1.3 (LE)
unnamed: C3.2, C4.1, L1.1
unnamed: C6.1, R9.2
unnamed: J1.1, U1.25 (LD)
unnamed: J1.2, U1.30 (MUXOUT)
unnamed: C7.1, R8.2, R9.1, U1.7 (CPout)
unnamed: R3.2, U1.22 (RSET)
unnamed: C5.1, R8.1, U1.20 (VTUNE)
unnamed: R2.1, U2.5 (RF2)
unnamed: C24.1, Y1.3 (OUTPUT)
Porteuse_RFC: C4.2, U2.4 (RFC)
REFIN: C24.2, U1.29 (REFIN)
RF1: J4.1 (In), U2.8 (RF1)
SCK: J2.2, R4.1, U1.1 (CLK)
TEMP: C8.1, C9.1, U1.19 (TEMP)
UART_RX: C1.1, J3.2, R1.1, U2.2 (CTRL)
VCOM: C10.1, C11.1, U1.23 (VCOM)
VREF: C12.1, C13.1, U1.24 (VREF)

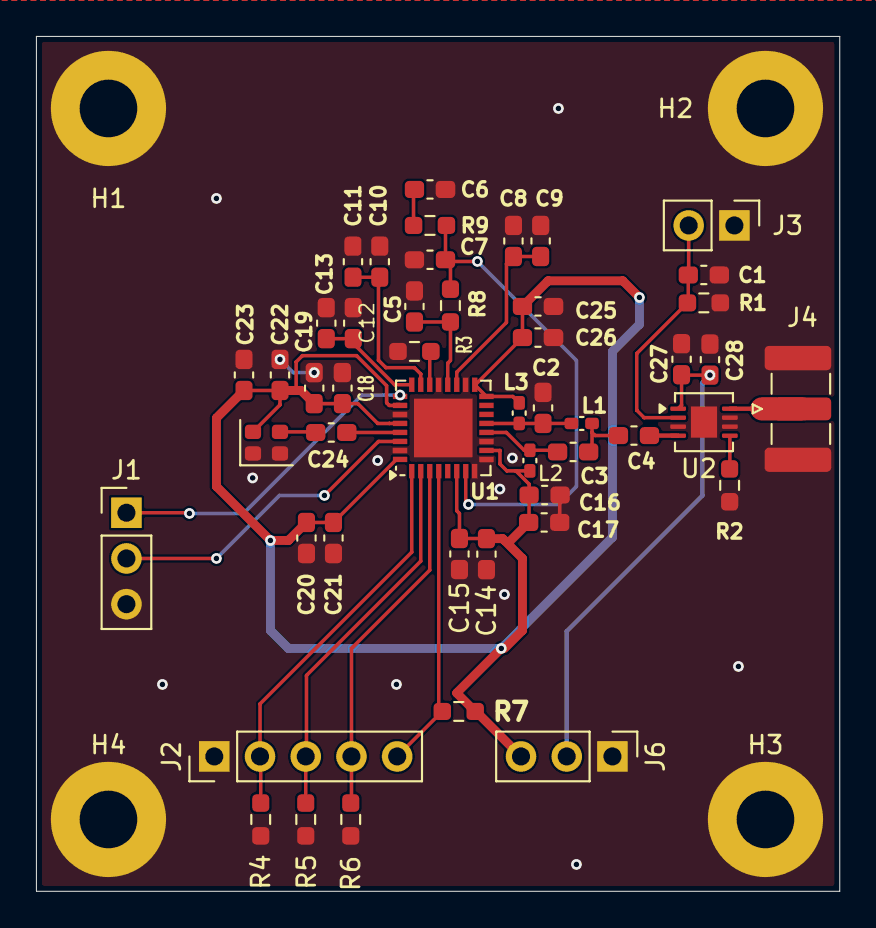
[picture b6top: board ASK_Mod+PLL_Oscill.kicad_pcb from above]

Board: 2 copper layers, 44.6 x 47.5 mm, 52 parts (0 on the bottom side), 25 nets.
